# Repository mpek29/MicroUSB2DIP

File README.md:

# MicroUSB2DIP

## 🚀 Overview

This is an open-source reverse-engineered version of a Micro USB to DIP adapter, based on the original component available [here](https://fr.aliexpress.com/item/32947889760.html). The goal of this project was to practice reverse engineering as a learning exercise and to prepare for a future adaptation in a larger project.

## 🎯 Purpose
- 🔍 **Reverse engineering**: Understanding the design and functionality of this micro USB  to DIP connector.
- 🛠️ **Skill development**: Enhancing expertise in PCB design and hardware analysis skills.
- 🔄 **Future adaptation**: Leveraging this knowledge for embedded applications.

## 📝 Features Comparison: Original vs. Reverse-Engineered

| Feature            | Original Module | Reverse-Engineered Version |
|--------------------|----------------|---------------------------|
| 🖥️ PCB Design        | Proprietary     | Open-source & customizable |
| 🔌 Connector Type    | Micro USB       | Micro USB |
| 📌 Pin Mapping      | Standard DIP    | Standard DIP |
| 👐 Mechanical Drawing  |  |  |
| 📝 Reverse-Engineered Schematic | N/A |  |
| 📷 Photo             |  |  |

## 🛠️ How to Use
### 📌 Wiring Guide
| Pin  | Function |  
|------|----------|  
| VBUS | +5V |  
| D-   | Data - |  
| D+   | Data + |  
| ID   | Mode detect (A: GND, B: Open) |  
| GND  | Ground |  

## 🌟 License
This project is open-source. Feel free to use, modify, and contribute! 🚀

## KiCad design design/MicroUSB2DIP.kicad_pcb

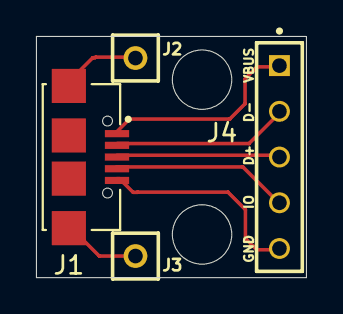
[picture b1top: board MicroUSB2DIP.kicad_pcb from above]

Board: 2 copper layers, 15.0 x 13.4 mm, 4 parts (0 on the bottom side), 6 nets.

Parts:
J1: UJ2-MIBH-G-SMT-TR; CUI_UJ2-MIBH-G-SMT-TR
J2, J3: TS-101-X-A-1; SAMTEC_TS-101-X-A-1
J4: TS-105-T-A-1; SAMTEC_TS-105-T-A-1

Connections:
D+: J1.3 (D+), J4.03
D-: J1.2 (D-), J4.02
GND: J1.5 (GND), J4.05
IO: J1.4 (ID), J4.04
Shield: J1.S1 (SHIELD), J1.S2 (SHIELD), J1.S3 (SHIELD), J1.S4 (SHIELD), J2.01, J3.01
VCC: J1.1 (VCC), J4.01

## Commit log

2025-02-05 Rename 5v_con.png to MicroUSB2DIP_Pinout_References.png
2025-02-07 completed project
2025-02-07 pictures edit
2025-02-07 deleted MicroUSB2DIP_Pinout_References.png
2025-02-07 Edit images
2025-02-19 Addition of some images to better describe the project
2025-02-20 new pic for sch
